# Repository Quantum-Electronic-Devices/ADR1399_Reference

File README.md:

# ADR1399 Sub-ppm Reference Voltage

This repository contains the KiCAD PCB project files for a sub-ppm temperature coefficient __negative voltage reference__ used in the [DgDrive laser current driver](https://qed.gmbh/en/products/electronics/dgdrive/).

## Circuit description

This circuit utilizes the excellent [ADR1399](https://www.analog.com/en/products/adr1399.html)/[LM399](https://www.analog.com/en/products/lm399.html) voltage reference and outputs an amplified voltage of either -10 V or -15 V. There is no option to trim the output voltage as the absolute value is not that important, but stability is. The output voltage will be 10 V / 15 V __below__ the positive pin of the Zener diode.

The design is a self-biased circuit, which means the Zener diode bias current is produced by the Zener voltage and therefore as stable as the reference (neglecting the influence of the bias current on the Zener voltage as it is negligible). In order to keep the Zener self-heating of the diode as low possible, a Zener current of a little more than 3 mA was chosen for the [ADR1399](https://www.analog.com/en/products/adr1399.html).

Reference table for choosing the resistor values:

|Voltage | R1       |    RN1        |
|------------|-----------|---------------|
|-10 V      | 3k        | 20k /  9k  |
|-15 V      | 7.89k | 17k / 20k |

Different values are possible as well, but these values were readily available on Farnell/Mouser. When choosing a value for R1, choose a value as close as possible but always __less than or equal__ to the value given. This ensures, that the Zener current is at least 1 mA.

Single supply operation is possible as long the output voltage is larger than 0.1 V (referenced to GND).

## Design Files
### For production
The design files required for the PCB production and assembly can be found on the [releases](../../releases) page and include the following resources:

- Schematics as a PDF
- Gerber files
- Pick & place position files
- Bill of materials as a CSV file and also as an interactive HTML version

The latest revision of those files can be found [here](../../releases/latest).

#### Variants
Two variants of the design files are provided for the user. There is a so-called *default* variant and a *PCBA* (Printed Circuit Board Assembly) variant.

##### Default variant
The default variant contains the full set of components and should be used for hand assembly when a set of binned and tested components is available. It includes both the Zener reference and resistive divider which need to be tested for popcorn noise and drift before installation.

##### PCBA variant
The PCBA variant should be used when sending the boards to the PCB manufacturer for assembly as they do not contain the [ADR1399](https://www.analog.com/en/products/adr1399.html)/[LM399](https://www.analog.com/en/products/lm399.html) Zener reference and the precision resistor array to amplify the output voltage. These components need to be binned prior to installation and should therefore not be placed by the board house.

### For editing
To work on the [KiCad](https://www.kicad.org/) design files, a number of external libraries are needed. Those libraries show up as empty folders in the zip file, because they are not included in the release, but must be downloaded separately from the links given [below](#related-repositories). This can be avoided by checking out the whole repository using git. This way the libraries will be downloaded as well. Use the following command to clone the git repository along with the submodules  using the `--recurse-submodules` flag.
```
git clone --recurse-submodules https://github.com/Quantum-Electronic-Devices/ADR1399_Reference
```

## Related Repositories
See the following repositories for more information as these are part of the [design files](#design Files).

- [KiCad footprints](https://github.com/PatrickBaus/footprints.pretty)
- [KiCAD 3D models](https://github.com/PatrickBaus/footprints.3dshapes)
- [KiCAD schematic libraries](https://github.com/PatrickBaus/KiCad-libraries)

## Versioning
We use [SemVer](http://semver.org/) for versioning. For the versions available, see the [tags](../../tags) available for this repository.

- MAJOR versions in this context mean a breaking change to the external interface of the hardware like different connectors or functions.
- MINOR versions contain changes to the hardware that only affect the inner workings of the circuit, but otherwise the performance is unaffected.
- PATCH versions do not affect the schematics or invalidate older bill of materials. These changes may include updated components (to replace obsolete parts for example), an updated silkscreen, or fixed typos.

## License
This work is released under the CERN-OHL-W
See [https://ohwr.org/cern_ohl_w_v2.pdf](https://ohwr.org/cern_ohl_w_v2.pdf) or the included LICENSE file for more information.

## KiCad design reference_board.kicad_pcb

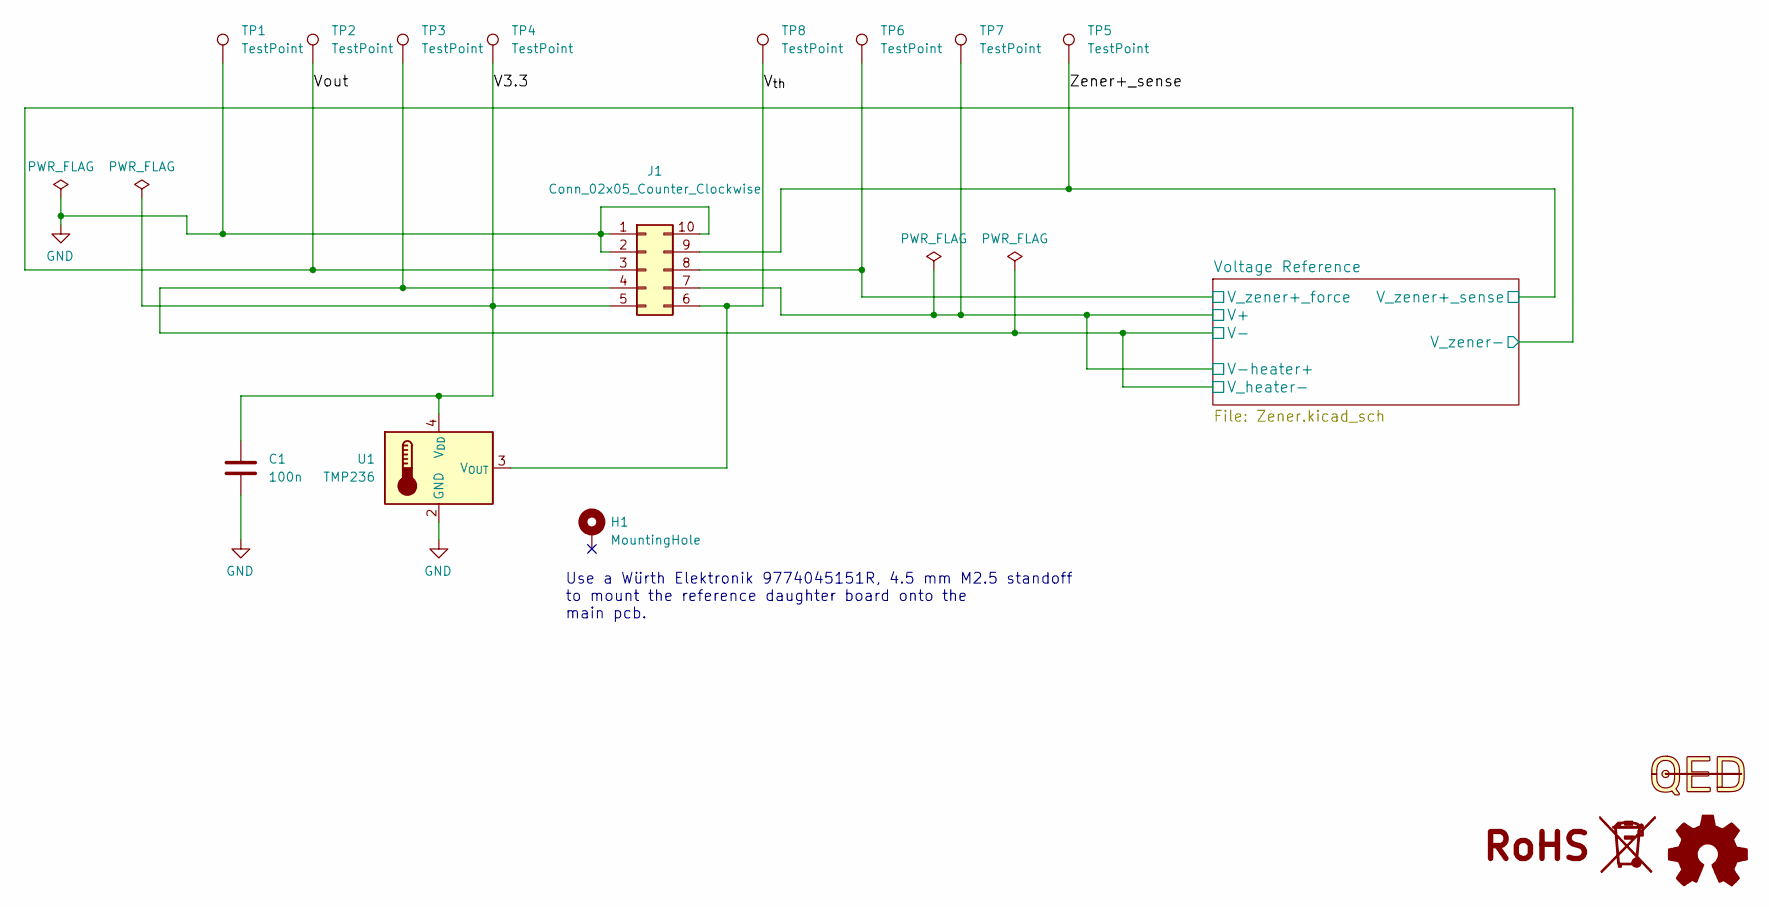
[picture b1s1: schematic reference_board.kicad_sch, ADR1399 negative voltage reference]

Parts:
C1: 100n; C_0603_1608Metric; farnell# 2070398
H1: MountingHole; MountingHole_2.7mm_M2.5_DIN965_Pad
J1: Conn_02x05_Counter_Clockwise; Molex_SlimStack_53307-1071_2x05_P0.80mm_Vertical
LOGO1: Logo_Open_Hardware_Small; OSHW-Logo2_7.3x6mm_SilkScreen
LOGO2: Logo_QED; QED-logo_small
SYM2: SYM_WEEE; WEEE-Logo_4.2x6mm_SilkScreen
TP1, TP2, TP3, TP4, TP5, TP6, TP7, TP8: TestPoint; TestPoint_Pad_D1.5mm
U1: TMP236; SOT-353_SC-70-5

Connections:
/V3.3: C1.1, J1.5, TP4.1 (1_1), U1.4 (V_{DD})
/V_{th}: J1.6, TP8.1 (1_1), U1.3 (V_{OUT})
/Voltage Reference/V+: J1.7, TP7.1 (1_1); also elsewhere on the board
/Voltage Reference/V-: J1.4, TP3.1 (1_1); also elsewhere on the board
/Voltage Reference/V_zener+_force: J1.8, TP6.1 (1_1); also elsewhere on the board
/Vout: J1.3, TP2.1 (1_1); also elsewhere on the board
/Zener+_sense: J1.9, TP5.1 (1_1); also elsewhere on the board
GND: C1.2, J1.1, J1.2, J1.10, TP1.1 (1_1), U1.2 (GND), U1.5 (GND); also elsewhere on the board

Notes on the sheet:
Use a Würth Elektronik 9774045151R, 4.5 mm M2.5 standoff to mount the reference daughter board onto the main pcb.

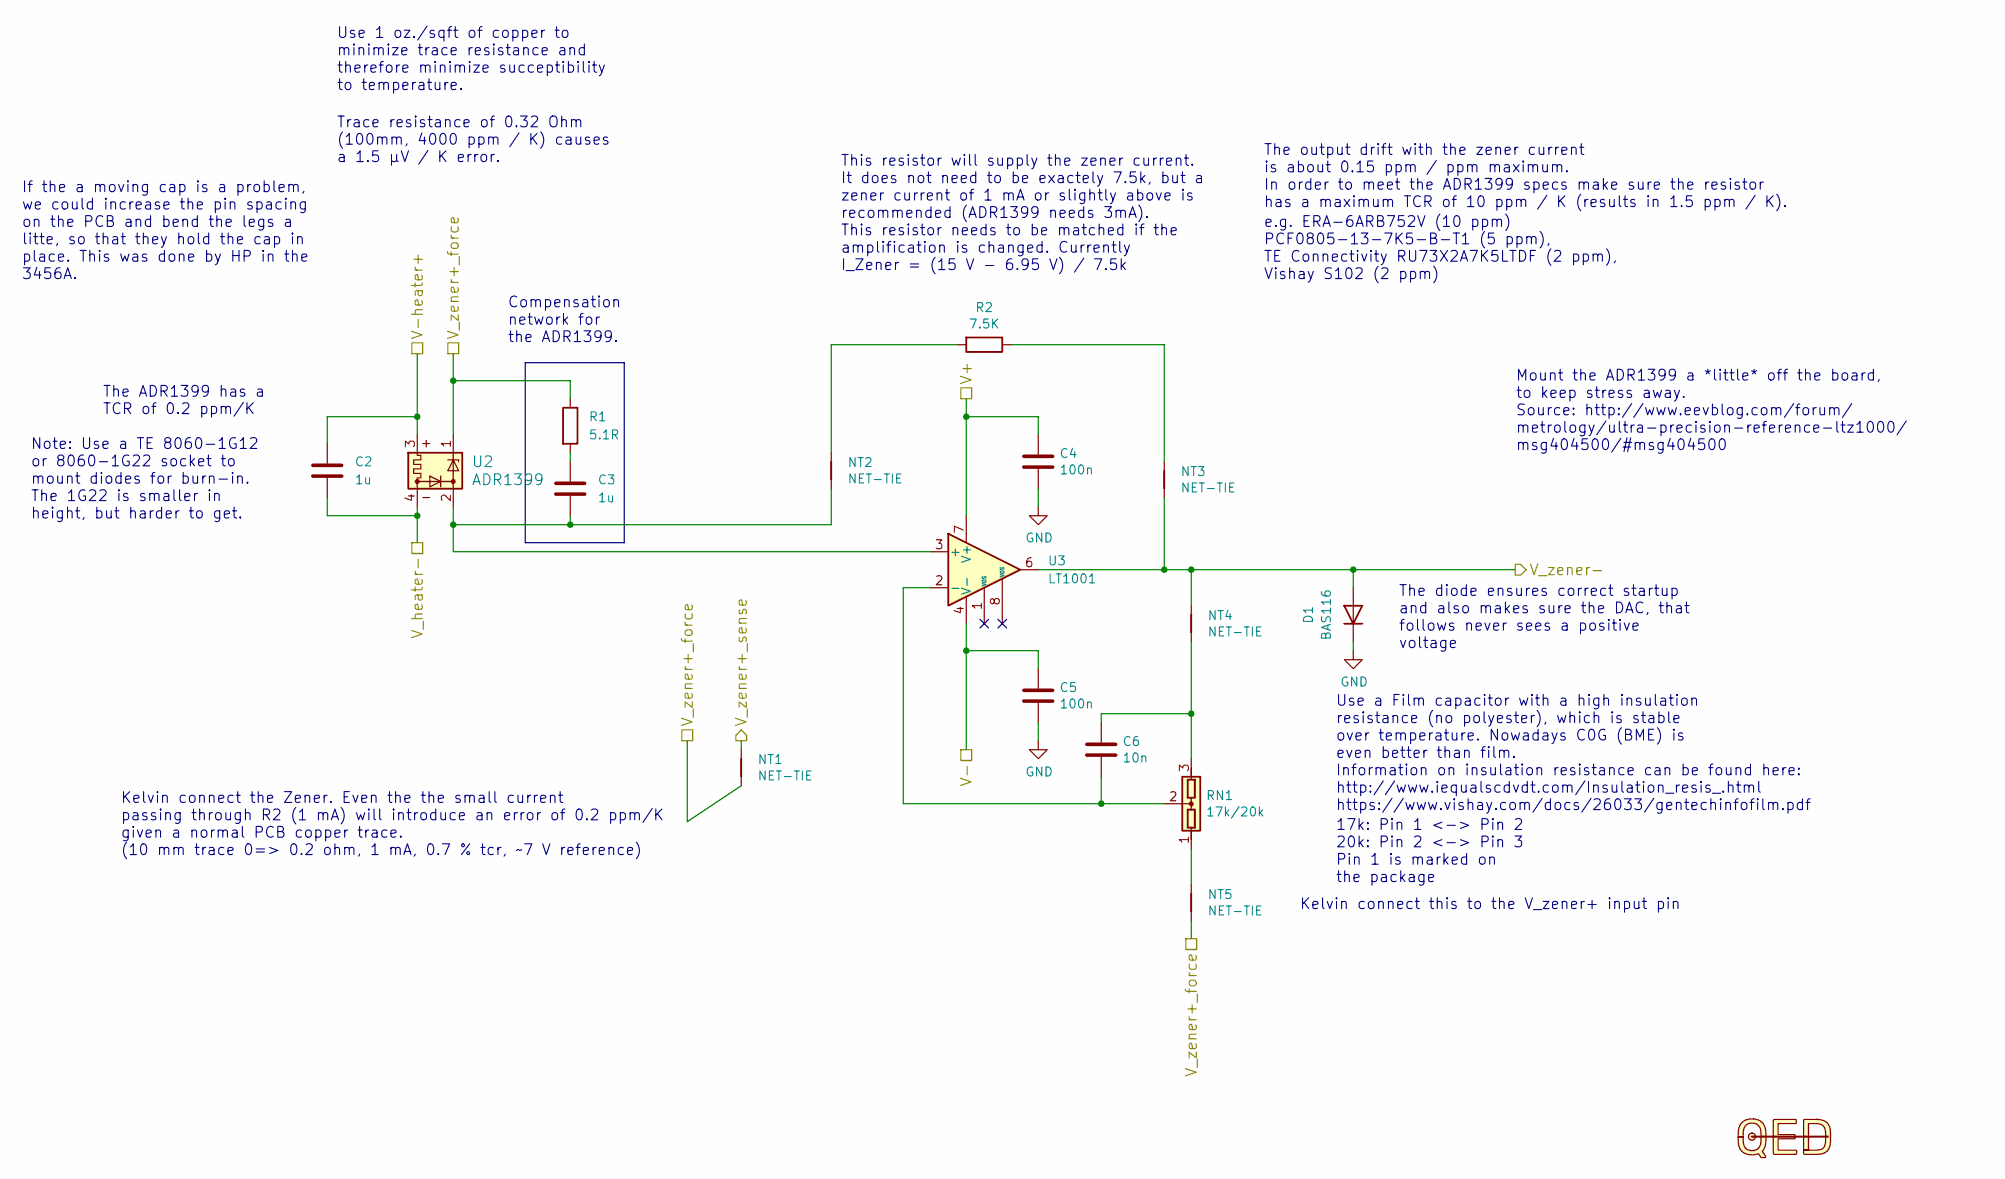
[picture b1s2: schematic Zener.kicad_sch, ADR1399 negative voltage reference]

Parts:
C2, C3: 1u; C_0603_1608Metric; farnell# 3228096
C4, C5: 100n; C_0603_1608Metric; farnell# 2070398
C6: 10n; C_0603_1608Metric
D1: BAS116; D_SOD-123F
NT1: NET-TIE; NET-TIE-0.15mm
NT2, NT3, NT4, NT5: NET-TIE; NET-TIE-0.25mm
R1: 5.1R; R_0603_1608Metric
R2: 7.5K; R_0805_2012Metric
RN1: 17k/20k; R_Array_Box3_L7.5mm_W2.5mm_P2.54mm_Vishay_300144
U2: ADR1399; Analog_TO-46-4_ThermalShield
U3: LT1001; SOIC-8_3.9x4.9mm_P1.27mm; farnell# 4217953

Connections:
/Voltage Reference/V+: C2.1, C4.1, U2.3, U3.7 (V+); also elsewhere on the board
/Voltage Reference/V-: C2.2, C5.1, U2.4, U3.4 (V-); also elsewhere on the board
/Voltage Reference/V_zener+_force: NT1.2, NT5.2, R1.1, U2.1; also elsewhere on the board
/Vout: D1.2 (A), NT3.2, NT4.1, U3.6; also elsewhere on the board
/Zener+_sense: NT1.1; also elsewhere on the board
GND: C4.2, C5.2, D1.1 (K); also elsewhere on the board
unnamed: C3.1, R1.2
unnamed: C6.1, NT4.2, RN1.3
unnamed: NT2.1, R2.2
unnamed: NT3.1, R2.1
unnamed: NT5.1, RN1.1
unnamed: C3.2, NT2.2, U2.2, U3.3 (+)
unnamed: C6.2, RN1.2, U3.2 (-)

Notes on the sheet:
17k: Pin 1 <-> Pin 2 20k: Pin 2 <-> Pin 3 Pin 1 is marked on the package
e.g. ERA-6ARB752V (10 ppm) PCF0805-13-7K5-B-T1 (5 ppm), TE Connectivity RU73X2A7K5LTDF (2 ppm), Vishay S102 (2 ppm)
Trace resistance of 0.32 Ohm (100mm, 4000 ppm / K) causes a 1.5 µV / K error.
Kelvin connect the Zener. Even the the small current passing through R2 (1 mA) will introduce an error of 0.2 ppm/K given a normal PCB copper trace. (10 mm trace 0=> 0.2 ohm, 1 mA, 0.7 % tcr, ~7 V reference)
Mount the ADR1399 a *little* off the board, to keep stress away. Source: http://www.eevblog.com/forum/ metrology/ultra-precision-reference-ltz1000/ msg404500/#msg404500
Kelvin connect this to the V_zener+ input pin
Note: Use a TE 8060-1G12 or 8060-1G22 socket to mount diodes for burn-in. The 1G22 is smaller in height, but harder to get.
This resistor will supply the zener current. It does not need to be exactely 7.5k, but a zener current of 1 mA or slightly above is recommended (ADR1399 needs 3mA). This resistor needs to be matched if the amplification is changed. Currently I_Zener = (15 V - 6.95 V) / 7.5k
The output drift with the zener current is about 0.15 ppm / ppm maximum. In order to meet the ADR1399 specs make sure the resistor has a maximum TCR of 10 ppm / K (results in 1.5 ppm / K).
Use 1 oz./sqft of copper to minimize trace resistance and therefore minimize succeptibility to temperature.
If the a moving cap is a problem, we could increase the pin spacing on the PCB and bend the legs a litte, so that they hold the cap in place. This was done by HP in the 3456A.
The ADR1399 has a TCR of 0.2 ppm/K
Compensation network for the ADR1399.
Use a Film capacitor with a high insulation resistance (no polyester), which is stable over temperature. Nowadays C0G (BME) is even better than film. Information on insulation resistance can be found here: http://www.iequalscdvdt.com/Insulation_resis_.html https://www.vishay.com/docs/26033/gentechi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
The diode ensures correct startup and also makes sure the DAC, that follows never sees a positive voltage

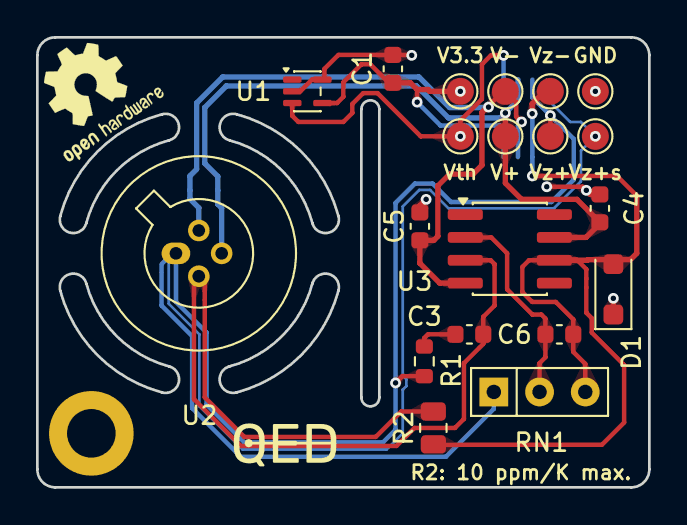
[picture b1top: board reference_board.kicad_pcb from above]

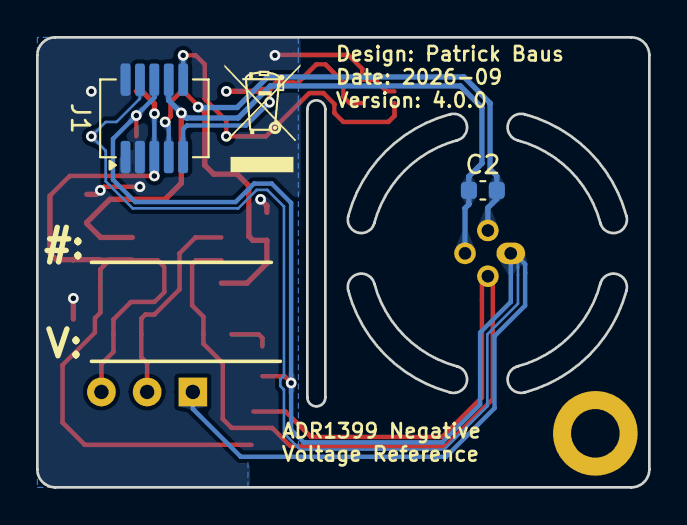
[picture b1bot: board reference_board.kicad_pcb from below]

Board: 2 copper layers, 34.0 x 25.0 mm, 31 parts (5 on the bottom side), 15 nets.

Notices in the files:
README.md:
License: CERN-OHL-W-2.0
Zener.kicad_sch:
Copyright (©) 2026, Patrick Baus
Licensed under CERN OHL-W v2.0
parts and their libraries:
Copyright Quantum Electronic Devices
Copyright Quantum Electronic Devices GmbH
